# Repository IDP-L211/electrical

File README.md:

# Team Optimal Electrical Design

This repository contains schematics and PCB layouts for the electronics of the
Team Optimal IDP robots. We operate with two PCBs: the Main PCB and the Color
Sensors PCB.

Note that Tim hasn't set up the library locations properly (because he'd rather
sleep). Just replace all occurences of `/home/tim/idp/electrical` with the
location of this repository and you should be fine.

## System diagram

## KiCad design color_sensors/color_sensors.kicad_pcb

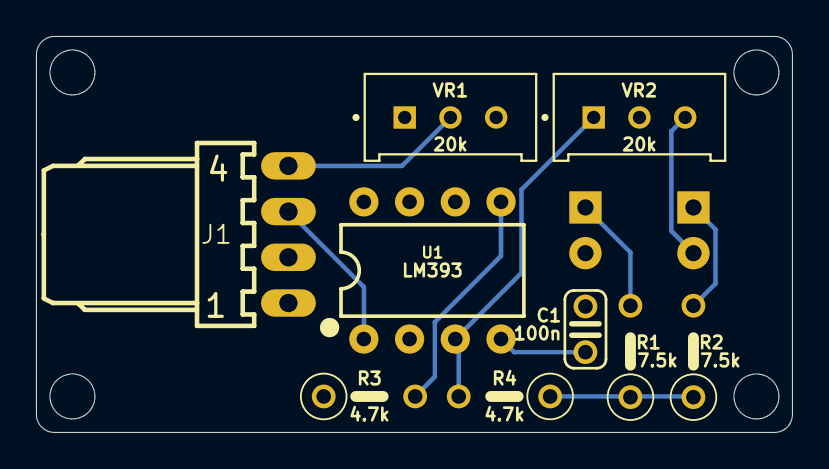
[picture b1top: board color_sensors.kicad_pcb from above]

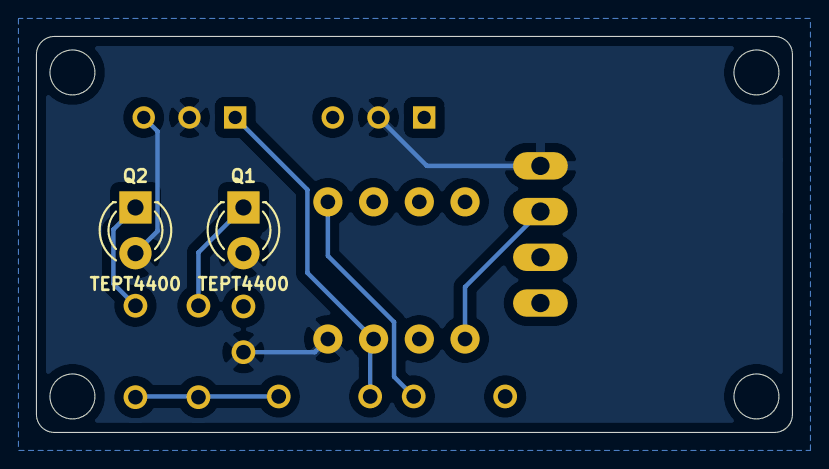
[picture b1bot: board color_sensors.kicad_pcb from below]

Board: 2 copper layers, 42.0 x 22.0 mm, 11 parts (2 on the bottom side), 8 nets.

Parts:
C1: 100n; IDP_library_C025-024X044
J1: 22-05-7048-04; IDP_library_7395-04
Q1, Q2: TEPT4400; LED_D3.0mm_Clear
R1, R2: 7.5k; IDP_library_0207_5V
R3, R4: 4.7k; IDP_library_0207_5V
U1: LM393; IDP_library_DIP08
VR1, VR2: 20k; IDP_library_TRIM_3296W-1-250

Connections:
+5V: C1.1, J1.1, R1.1, R2.1, R3.1, R4.1, U1.8
/green: J1.3, U1.1
/red: J1.2, U1.7
GND: C1.2, J1.4, Q1.2, Q2.2, U1.4, VR1.2, VR2.2
unnamed: Q1.1, R1.2, U1.6
unnamed: Q2.1, R2.2, U1.2
unnamed: R3.2, U1.5, VR1.1
unnamed: R4.2, U1.3, VR2.1

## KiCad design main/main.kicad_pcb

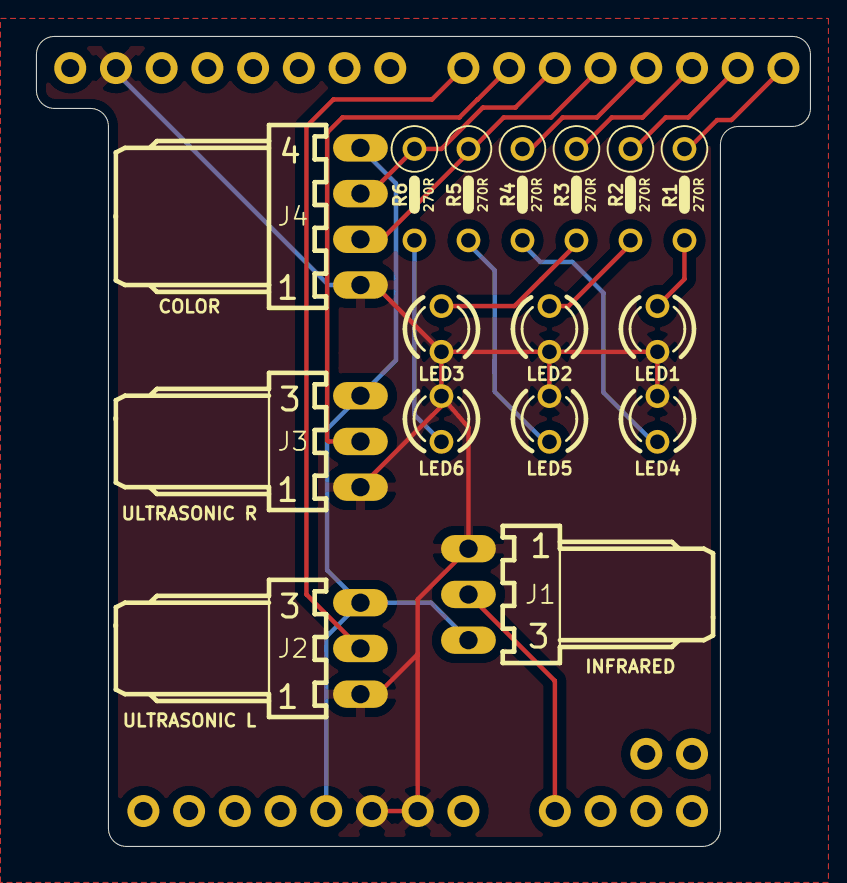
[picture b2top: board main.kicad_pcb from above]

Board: 16 copper layers, 43.0 x 45.0 mm, 21 parts (0 on the bottom side), 17 nets.

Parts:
CN1: 1X4-CLEANBIG; 1X04-CLEANBIG
D0-1: PINHD-1X8CLEANBIG; 1X08-CLEANBIG
J1, J2, J3: 22-05-7038-03; IDP_library_7395-03
J4: 22-05-7048-04; IDP_library_7395-04
JP2: HEADER-1X2ROUND; 1X02_ROUND
JP3: PINHD-1X8CLEANBIG; 1X08-CLEANBIG
JP4: HEADER-1X1070MIL; 1X10_ROUND70
LED1, LED2, LED3: BLUE_3MM; IDP_library_LED3MM
LED4: YELLOW_3MM; IDP_library_LED3MM
LED5: RED_3MM; IDP_library_LED3MM
LED6: GREEN_3MM; IDP_library_LED3MM
R1, R2, R3, R4, R5, R6: 270R; IDP_library_0207_5V

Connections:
+5V: J1.3, J2.3, J3.3, J4.4, JP3.4
/green: D0-1.6, J4.3, R6.1
/infra_red: CN1.4, J1.2
/proximity: D0-1.4, R4.1
/red: D0-1.5, J4.2, R5.1
/status_0: D0-1.1, R1.1
/status_1: D0-1.2, R2.1
/status_2: D0-1.3, R3.1
/ultrasonic_left: D0-1.8, J2.2
/ultrasonic_right: D0-1.7, J3.2
GND: J1.1, J2.1, J3.1, J4.1, JP3.2, JP3.3, JP4.4, LED1.K, LED2.K, LED3.K, LED4.K, LED5.K, LED6.K
unnamed: LED1.A, R1.2
unnamed: LED2.A, R2.2
unnamed: LED3.A, R3.2
unnamed: LED4.A, R4.2
unnamed: LED5.A, R5.2
unnamed: LED6.A, R6.2

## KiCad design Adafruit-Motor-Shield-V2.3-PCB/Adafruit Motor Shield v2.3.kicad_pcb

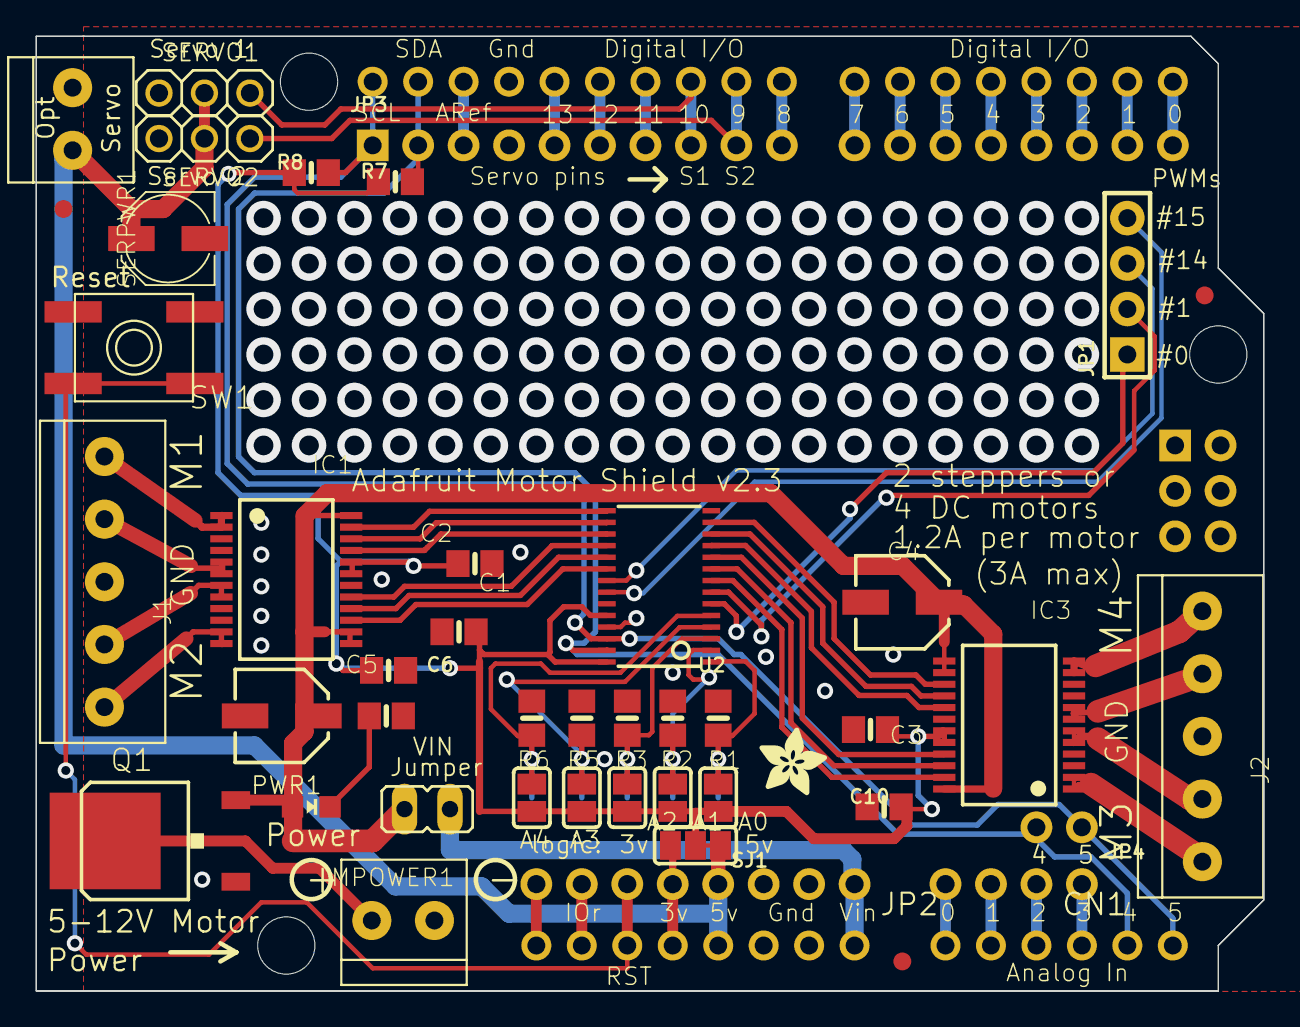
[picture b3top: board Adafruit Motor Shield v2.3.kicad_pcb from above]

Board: 16 copper layers, 68.6 x 53.3 mm, 55 parts (0 on the bottom side), 61 nets.

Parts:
@HOLE0, @HOLE1, @HOLE2: (no value)
A0, A1, A2, A3, A4: SOLDERJUMPERREFLOW_NOPASTE; SOLDERJUMPER_REFLOW_NOPASTE
C1, C2, C3: 0.1uF; 0805-NO
C4: 47uF/16v; PANASONIC_C
C5: 47uF+/16v; PANASONIC_C
C6, C10: 10uF; 0805-NO
C9: 10\0uF 6.3V; PANASONIC_C
CN1: 1X4-CLEANBIG; 1X04-CLEANBIG
D0-7: PINHD-1X8CLEANBIG; 1X08-CLEANBIG
IC1, IC3: TB6612FNG; SSOP24
J1, J2: 1X5; 1X05-3.5MM
JP1: HEADER-1X476MIL; 1X04_ROUND_76
JP2: PINHD-1X8CLEANBIG; 1X08-CLEANBIG
JP3: HEADER-1X1070MIL; 1X10_ROUND70
JP4: HEADER-1X2ROUND; 1X02_ROUND
LED1: Green; CHIPLED_0805_NOOUTLINE
MPOWER1: 1X2-3.5MM
PWR1: JP1E; JP1
Q1: AOD417; D-PAK_TO252AA
R1, R2, R3, R5, R6: 10k; 0805-NO
R4: 1K; 0805-NO
R7, R8: 10K; 0805-NO
SERPWR1: 1X2-3.5MM
SERVO1, SERVO2: PINHD-1X3; 1X03
SJ1: SOLDERJUMPER_2WAY; SOLDERJUMPER_2WAY_OPEN_NOPASTE
SW1: SPST_TACT-EVQQ2; EVQ-Q2
TP1, TP2, TP3, TP4, TP5: TESTPOINTROUND2MM; TESTPOINT_ROUND_2MM
U2: PCA9685; TSSOP28
U$1: ARDUINO_R3_ICSP; ARDUINOR3_ICSP
U$2, U$3, U$4: FIDUCIAL; FIDUCIAL_1MM
U$5: ADAFRUIT_TEXT_30MM
U$6: ADAFRUIT_3.5MM

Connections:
+3V3: JP2.5, SJ1.3, U$1.3V
+5V: C9.+, JP2.4, SERPWR1.1, SERVO1.2, SERVO2.2, SJ1.1, U$1.5V, U$1.5V_ICSP
+12V: C4.+, C5.+, IC1.13, IC1.14, IC1.24, IC3.13, IC3.14, IC3.24, LED1.A, PWR1.1, Q1.3
//RST: JP2.6, SW1.B, SW1.B', U$1.RESET, U$1.RESET_ICSP
/A0: A0.2, R1.2, TP5.P$1, U2.1
/A1: A1.2, R2.2, TP4.P$1, U2.2
/A2: A2.2, R3.2, TP3.P$1, U2.3
/A3: A3.1, R5.2, TP2.P$1, U2.4
/A4: A4.1, R6.2, TP1.P$1, U2.5
/AD4/SDA: JP3.2, JP4.2, R7.1, U2.27, U$1.A4, U$1.SDA
/AD5/SCL: JP3.1, JP4.1, R8.1, U2.26, U$1.A5, U$1.SCL
/D9: JP3.9, SERVO2.3, U$1.D9
/D10: JP3.8, SERVO1.3, U$1.D10
/PWM0: JP1.1, U2.6
/PWM1: JP1.2, U2.7
/PWM2: IC3.23, U2.8
/PWM3: IC3.22, U2.9
/PWM4: IC3.21, U2.10
/PWM5: IC3.17, U2.11
/PWM6: IC3.16, U2.12
/PWM7: IC3.15, U2.13
/PWM8: IC1.23, U2.15
/PWM9: IC1.22, U2.16
/PWM10: IC1.21, U2.17
/PWM11: IC1.17, U2.18
/PWM12: IC1.16, U2.19
/PWM13: IC1.15, U2.20
/PWM14: JP1.3, U2.21
/PWM15: JP1.4, U2.22
/VIN: JP2.1, PWR1.2, U$1.VIN
GND: C1.2, C2.2, C3.2, C4.-, C5.-, C6.2, C9.-, C10.2, IC1.3, IC1.4, IC1.9, IC1.10, IC1.18, IC3.3, IC3.4, IC3.9, IC3.10, IC3.18, J1.3, J2.3, JP2.2, JP2.3, JP3.4, MPOWER1.1, Q1.1, R1.1, R2.1, R3.1, R4.1, R5.1, R6.1, SERPWR1.2, SERVO1.1, SERVO2.1, SW1.A, SW1.A', U2.14, U2.23, U2.25, U$1.GND, U$1.GND@1, U$1.GND@2, U$1.GND@3
unnamed: CN1.1, U$1.A3
unnamed: CN1.2, U$1.A2
unnamed: CN1.3, U$1.A1
unnamed: CN1.4, U$1.A0
unnamed: D0-7.1, U$1.D0
unnamed: D0-7.2, U$1.D1
unnamed: D0-7.3, U$1.D2
unnamed: D0-7.4, U$1.D3
unnamed: D0-7.5, U$1.D4
unnamed: D0-7.6, U$1.D5
unnamed: D0-7.7, U$1.D6
unnamed: D0-7.8, U$1.D7
unnamed: IC1.1, IC1.2, J1.5
unnamed: IC1.5, IC1.6, J1.4
unnamed: IC1.7, IC1.8, J1.2
unnamed: IC1.11, IC1.12, J1.1
unnamed: IC3.1, IC3.2, J2.1
unnamed: IC3.5, IC3.6, J2.2
unnamed: IC3.7, IC3.8, J2.4
unnamed: IC3.11, IC3.12, J2.5
unnamed: JP2.7, U$1.IOREF
unnamed: JP2.8, U$1.RESERVED
unnamed: JP3.3, U$1.AREF
unnamed: JP3.5, U$1.D13
unnamed: JP3.6, U$1.D12
unnamed: JP3.7, U$1.D11
unnamed: JP3.10, U$1.D8
unnamed: LED1.C, R4.2
unnamed: MPOWER1.2, Q1.4
VCC: A0.1, A1.1, A2.1, A3.2, A4.2, C1.1, C2.1, C3.1, C6.1, C10.1, IC1.19, IC1.20, IC3.19, IC3.20, R7.2, R8.2, SJ1.2, U2.24, U2.28

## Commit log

2021-02-18 Add libraries
2021-02-18 Add kicad 5 files to gitignore
2021-02-18 Cleanup
2021-02-18 Reformat the conversion log
    Because OCD or something idk.
2021-02-19 Edit library file to fix PCB automatic footprint referencing
2021-02-25 Add basic file structure
2021-02-28 First draft of schematic
2021-03-05 First draft of Main PCB and Color Sensors PCB
2021-03-06 Make STEP for Color Sensor PCB; remove ultrasonic PCB
2021-03-06 Add mounting holes to Color Sensor PCB
2021-03-06 Make STEP file compatible with SolidWorks' broken importer
2021-03-09 Specify resistors; neaten silkscreen; improve 3D model
2021-03-09 Add STEP files for new PCBs
2021-03-09 Add power and ground planes; update resistor values
2021-03-13 Submission candidate 1
2021-03-14 added system diagram
2021-03-14 Add system diagram to README.md
2021-03-14 added system lvl diagram SVG file
2021-03-16 Add PDF versions of schematics
2021-03-20 Tweak README.md
2021-03-20 Add LICENSE
2021-03-21 Add note about github repository to PCB output diagrams
2021-03-21 Final Documentation
